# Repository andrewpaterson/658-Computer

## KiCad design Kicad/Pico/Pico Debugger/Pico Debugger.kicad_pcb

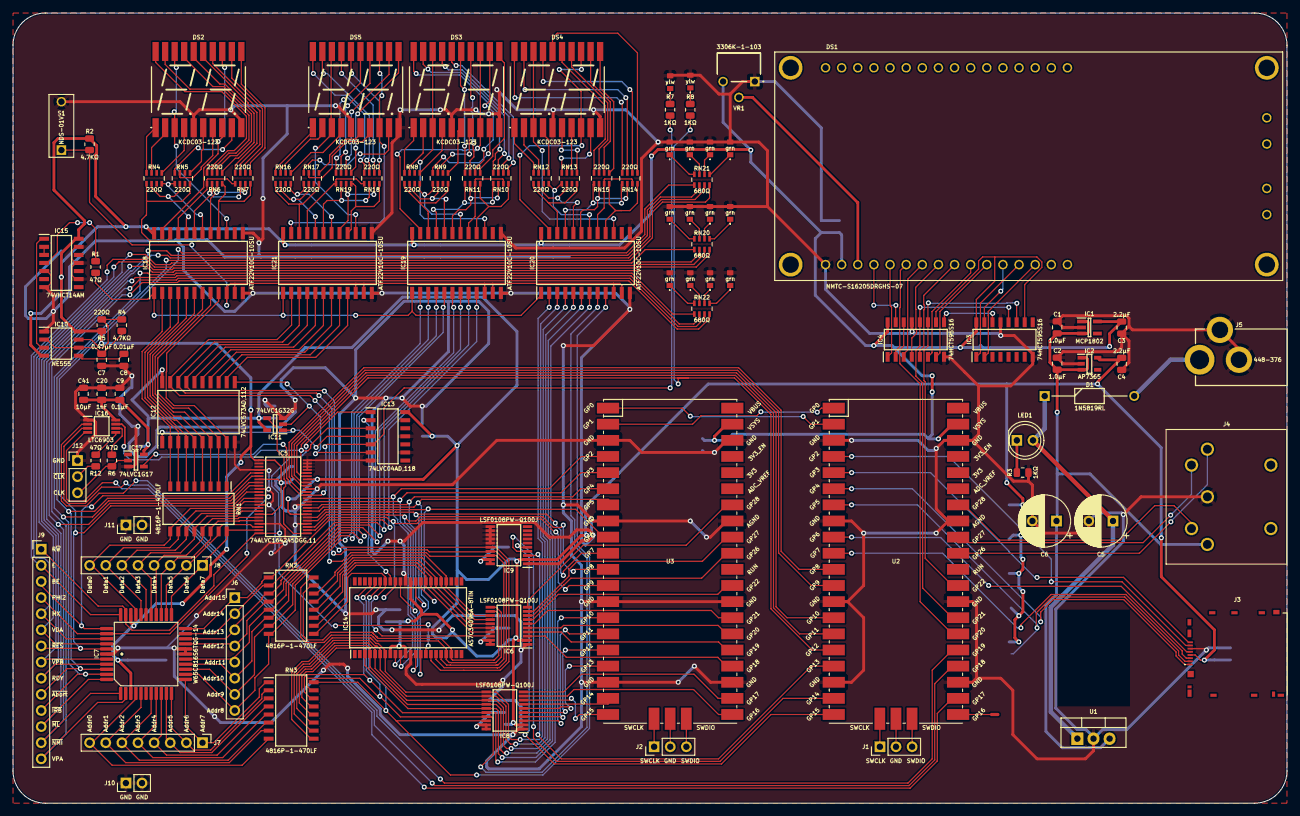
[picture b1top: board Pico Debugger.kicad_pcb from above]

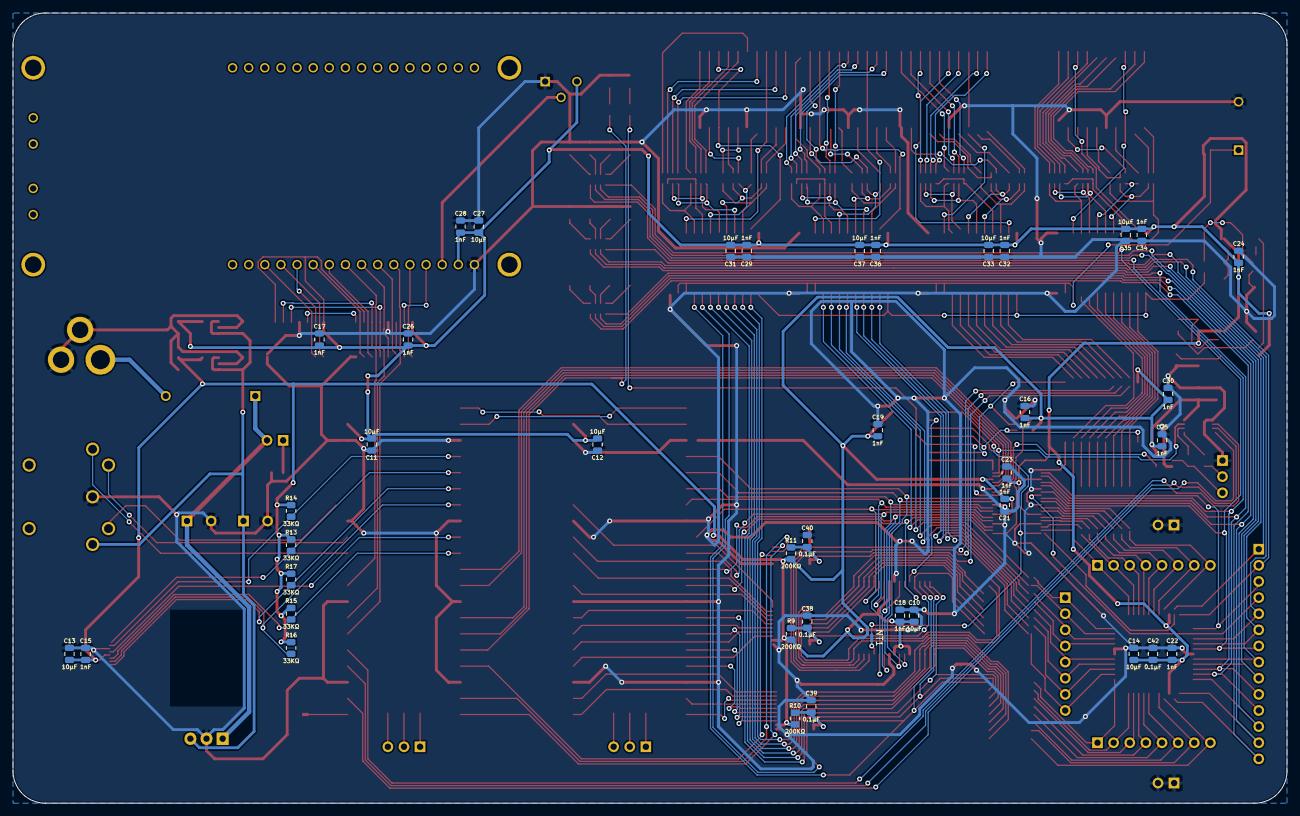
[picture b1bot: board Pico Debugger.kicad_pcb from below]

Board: 2 copper layers, 200.7 x 124.5 mm, 142 parts (40 on the bottom side), 273 nets.

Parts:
C1, C2, C3, C4, C7, C8, C9, C10, C11, C12, C13, C14, C15, C16, C17, C18, C19, C20, C21, C22, C23, C24, C25, C26, C27, C28, C29, C30, C31, C32, C33, C34, C35, C36, C37, C38, C39, C40, C41, C42: C_0805
C5, C6: C_Polarized; CP_Radial_D8.0mm_P3.80mm
D1: 1N5819RL; DIOAD1414W86L464D238
DS1: NMTC-S16205DRGHS-07; NMTCS16205DRGHS07_1
DS2, DS3, DS4, DS5: KCDC03-123; KCDC03123
IC1: MCP1802T-5002I_OT; SOT95P270X145-5N
IC2: AP7365-33WG-7; SOT95P285X130-5N
IC3, IC4: 74HCT595S16; SOIC127P600X175-16N
IC5: 74ALVC164245DGG,11; SOP50P810X120-48N
IC6, IC8, IC9: LSF0108PW-Q100J; SOP65P640X110-20N
IC7: W65C816S6TQG-14; W65C816 PLCC 0.8mm 44 Pin
IC10: NE555DRG4; SOIC127P600X175-8N
IC11: 74LVC1G32GV,125; SOT95P275X110-5N
IC12: 74LVC573AD,112; SOIC127P1032X265-20N
IC13: 74LVC04AD,118; SOIC127P600X175-14N
IC14: AS7C34096A-8TIN; SOP80P1176X120-44N
IC15: 74VHCT14AM; SOIC127P600X175-14N
IC16: LTC6903CMS8#PBF; SOP65P490X110-8N
IC17: 74LVC1G17GV,125; SOT95P275X110-5N
IC18, IC19, IC20, IC21: ATF22V10C-10SU; SOIC127P1032X265-24N
J1, J2, J12: Conn_01x03_Male; PinHeader_1x03_P2.54mm_Vertical
J3: SDHR-8BRS-K-363-A0-S-ETB(HF); SDHR8BRSK363A0SETBHF
J4: 491-087; 491087
J5: 448-376; 448376
J6, J7, J8: Conn_01x08_Male; PinHeader_1x08_P2.54mm_Vertical
J9: Conn_01x14_Male; PinHeader_1x14_P2.54mm_Vertical
J10, J11: Conn_01x02_Male; PinHeader_1x02_P2.54mm_Vertical
LED1: LED_Small_Filled; LED_D5.0mm
LED2, LED3: 150224YS73100A; 150224BS73100A
LED4, LED5, LED6, LED7, LED8, LED9, LED10, LED11, LED12, LED13, LED14, LED15: 150224VS73100A
NT1, NT2: NetTie; NetTie-2_SMD_Pad0.5mm
R1, R2, R3, R4, R5, R6, R7, R8, R9, R10, R11, R12, R13, R14, R15, R16, R17: R_0805
RN1, RN2, RN3: 4816P-1-470LF; SOIC127P762X240-16N
RN4, RN5, RN6, RN7, RN8, RN9, RN10, RN11, RN12, RN13, RN14, RN15, RN16, RN17, RN18, RN19: CAY16-221J4LF; CAY1647R0F4LF
RN20, RN21, RN22: CAY16-681J4LF; CAY16-J4
S1: NDS-01V; NDS01V
U1: L7805; TO-220-3_Vertical
U2, U3: Pico; RPi_Pico_SMD
VR1: 3306K-1-103; 3306K1103

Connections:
/3.3V: C4.1, C9.1, C10.1, C13.1, C15.1, C16.1, C18.1, C19.1, C20.1, C21.1, C25.1, C30.1, C41.1, IC2.5 (VOUT), IC5.31 (3V), IC5.42 (3V), IC6.2 (REFA), IC8.2 (REFA), IC9.2 (REFA), IC11.5 (3V), IC12.20 (3V), IC13.14 (3V), IC14.8 (~CE), IC14.11 (3V), IC14.33 (3V), IC16.8 (V+), IC17.5 (3V), J3.4 (VDD), R9.1, R10.1, R11.1, R13.2, R14.2, R15.2, R16.2, R17.2
/5V: C3.1, C11.1, C12.1, C14.1, C17.1, C22.1, C23.1, C24.1, C26.1, C27.1, C28.1, C29.1, C31.1, C32.1, C33.1, C34.1, C35.1, C36.1, C37.1, C42.1, DS1.2 (5V), IC1.5 (VOUT), IC3.10 (~MR), IC3.16 (VCC), IC4.10 (~MR), IC4.16 (VCC), IC5.1 (1DIR), IC5.7 (5V), IC5.18 (5V), IC7.9 (VCC), IC7.37 (VCC), IC10.4 (RESET), IC10.8 (VCC), IC15.14 (5V), IC18.24 (5V), IC19.24 (5V), IC20.24 (5V), IC21.24 (5V), R2.2, R5.2, U2.39 (VSYS), U3.39 (VSYS), VR1.3 (VIN)
/5V Forward: C5.1, D1.1, LED1.2 (A), U1.1 (IN)
/5V Source: C1.1, C2.1, C6.1, IC1.1 (VIN), IC1.3 (~SHDN), IC2.1 (VIN), IC2.3 (EN), J4.3, U1.3 (OUT)
/300Hz: IC18.1 (CLK/IN), IC19.1 (CLK/IN), IC20.1 (CLK/IN), IC21.1 (CLK/IN), R1.1
/Addr0: IC8.11 (B7), IC14.7 (A0), IC20.2 (IN0), RN3.9
/Addr0_{Pico}: IC8.10 (A7), U3.22 (GPIO17)
/Addr0_{W65}: IC7.10 (A0), J7.8, RN3.8
/Addr1: IC8.12 (B6), IC14.6 (A1), IC20.3 (IN1), RN3.10
/Addr1_{Pico}: IC8.9 (A6), U3.21 (GPIO16)
/Addr1_{W65}: IC7.11 (A1), J7.7, RN3.7
/Addr2: IC8.13 (B5), IC14.5 (A2), IC20.4 (IN2/PD), RN3.11
/Addr2_{Pico}: IC8.8 (A5), U3.20 (GPIO15)
/Addr2_{W65}: IC7.13 (A2), J7.6, RN3.6
/Addr3: IC8.14 (B4), IC14.4 (A3), IC20.5 (IN3), RN3.12
/Addr3_{Pico}: IC8.7 (A4), U3.19 (GPIO14)
/Addr3_{W65}: IC7.14 (A3), J7.5, RN3.5
/Addr4: IC8.15 (B3), IC14.3 (A4), IC20.6 (IN4), RN3.13
/Addr4_{Pico}: IC8.6 (A3), U3.17 (GPIO13)
/Addr4_{W65}: IC7.15 (A4), J7.4, RN3.4
/Addr5: IC8.16 (B2), IC14.41 (A5), IC20.7 (IN5), RN3.14
/Addr5_{Pico}: IC8.5 (A2), U3.16 (GPIO12)
/Addr5_{W65}: IC7.16 (A5), J7.3, RN3.3
/Addr6: IC8.17 (B1), IC14.40 (A6), IC20.8 (IN6), RN3.15
/Addr6_{Pico}: IC8.4 (A1), U3.15 (GPIO11)
/Addr6_{W65}: IC7.17 (A6), J7.2, RN3.2
/Addr7: IC8.18 (B0), IC14.39 (A7), IC20.9 (IN7), RN3.16
/Addr7_{Pico}: IC8.3 (A0), U3.14 (GPIO10)
/Addr7_{W65}: IC7.18 (A7), J7.1, RN3.1
/Addr8: IC6.18 (B0), IC14.38 (A8), RN2.9
/Addr8_{Pico}: IC6.3 (A0), U3.24 (GPIO18)
/Addr8_{W65}: IC7.19 (A8), IC19.2 (IN0), J6.8, RN2.8
/Addr9: IC6.17 (B1), IC14.30 (A9), RN2.10
/Addr9_{Pico}: IC6.4 (A1), U3.25 (GPIO19)
/Addr9_{W65}: IC7.20 (A9), IC19.3 (IN1), J6.7, RN2.7
/Addr10: IC6.16 (B2), IC14.29 (A10), RN2.11
/Addr10_{Pico}: IC6.5 (A2), U3.26 (GPIO20)
/Addr10_{W65}: IC7.21 (A10), IC19.4 (IN2/PD), J6.6, RN2.6
/Addr11: IC6.15 (B3), IC14.28 (A11), RN2.12
/Addr11_{Pico}: IC6.6 (A3), U3.27 (GPIO21)
/Addr11_{W65}: IC7.22 (A11), IC19.5 (IN3), J6.5, RN2.5
/Addr12: IC6.14 (B4), IC14.27 (A12), RN2.13
/Addr12_{Pico}: IC6.7 (A4), U3.29 (GPIO22)
/Addr12_{W65}: IC7.25 (A12), IC19.6 (IN4), J6.4, RN2.4
/Addr13: IC6.13 (B5), IC14.26 (A13), RN2.14
/Addr13_{Pico}: IC6.8 (A5), U3.31 (GPIO26_ADC0)
/Addr13_{W65}: IC7.26 (A13), IC19.7 (IN5), J6.3, RN2.3
/Addr14: IC6.12 (B6), IC14.20 (A14), RN2.15
/Addr14_{Pico}: IC6.9 (A6), U3.32 (GPIO27_ADC1)
/Addr14_{W65}: IC7.27 (A14), IC19.8 (IN6), J6.2, RN2.2
/Addr15: IC6.11 (B7), IC14.19 (A15), RN2.16
/Addr15_{Pico}: IC6.10 (A7), U3.34 (GPIO28_ADC2)
/Addr15_{W65}: IC7.28 (A15), IC19.9 (IN7), J6.1, RN2.1
/Addr16: IC9.18 (B0), IC12.19 (Q0), IC14.18 (A16), IC21.2 (IN0)
/Addr16_{Pico}: IC9.3 (A0), U2.17 (GPIO13)
/Addr17: IC9.17 (B1), IC12.18 (Q1), IC14.17 (A17), IC21.3 (IN1)
/Addr17_{Pico}: IC9.4 (A1), U2.19 (GPIO14)
/Addr18: IC9.16 (B2), IC12.17 (Q2), IC14.16 (A18), IC21.4 (IN2/PD)
/Addr18_{Pico}: IC9.5 (A2), U2.20 (GPIO15)
/Addr19: IC12.16 (Q3), IC21.5 (IN3)
/Addr20: IC12.15 (Q4), IC21.6 (IN4)
/Addr21: IC12.14 (Q5), IC21.7 (IN5)
/Addr22: IC12.13 (Q6), IC21.8 (IN6)
/Addr23: IC12.12 (Q7), IC21.9 (IN7)
/BE: IC5.44 (1A2), IC13.3 (2A), IC16.7 (OE), R8.1, U2.16 (GPIO12)
/BE_{W65}: IC5.5 (1B2), IC7.40 (BE), J9.3
/Bank Address Display/Digit 0 A Seg: IC21.17 (I/O3), RN18.7 (R2), RN19.7 (R2)
/Bank Address Display/Digit 0 B Seg: IC21.16 (I/O2), RN18.8 (R1), RN19.8 (R1)
/Bank Address Display/Digit 0 C Seg: IC21.18 (I/O4), RN16.4 (R4), RN17.1 (R1)
/Bank Address Display/Digit 0 D Seg: IC21.20 (I/O6), RN16.2 (R2), RN17.2 (R2)
/Bank Address Display/Digit 0 E Seg: IC21.22 (I/O8), RN16.1 (R1), RN17.4 (R4)
/Bank Address Display/Digit 0 F Seg: IC21.19 (I/O5), RN18.6 (R3), RN19.6 (R3)
/Bank Address Display/Digit 0 G Seg: IC21.21 (I/O7), RN18.5 (R4), RN19.5 (R4)
/Bank Address Display/Digit L0 Cathode: DS5.3 (Cathode_{(Left)}), DS5.18 (Cathode_{(Left)}), IC21.15 (I/O1)
/Bank Address Display/Digit R0 Cathode: DS5.8 (Cathode_{(Right)}), DS5.13 (Cathode_{(Right)}), IC21.23 (I/O9)
/Clk: IC16.6 (CLK), R6.1
/Data0: IC5.36 (2A0), IC14.9 (DQ0), U3.4 (GPIO2)
/Data0_{W65}: IC5.13 (2B0), IC7.36 (D0), J8.8, RN1.9
/Data1: IC5.35 (2A1), IC14.10 (DQ1), U3.5 (GPIO3)
/Data1_{W65}: IC5.14 (2B1), IC7.35 (D1), J8.7, RN1.10
/Data2: IC5.33 (2A2), IC14.13 (DQ2), U3.6 (GPIO4)
/Data2_{W65}: IC5.16 (2B2), IC7.34 (D2), J8.6, RN1.11
/Data3: IC5.32 (2A3), IC14.14 (DQ3), U3.7 (GPIO5)
/Data3_{W65}: IC5.17 (2B3), IC7.33 (D3), J8.5, RN1.12
/Data4: IC5.30 (2A4), IC14.31 (DQ4), U3.9 (GPIO6)
/Data4_{W65}: IC5.19 (2B4), IC7.32 (D4), J8.4, RN1.13
/Data5: IC5.29 (2A5), IC14.32 (DQ5), U3.10 (GPIO7)
/Data5_{W65}: IC5.20 (2B5), IC7.31 (D5), J8.3, RN1.14
/Data6: IC5.27 (2A6), IC14.35 (DQ6), U3.11 (GPIO8)
/Data6_{W65}: IC5.22 (2B6), IC7.30 (D6), J8.2, RN1.15
/Data7: IC5.26 (2A7), IC14.36 (DQ7), U3.12 (GPIO9)
/Data7_{W65}: IC5.23 (2B7), IC7.29 (D7), J8.1, RN1.16
/Data Display/Digit 0 A Seg: IC18.17 (I/O3), RN6.7 (R2), RN7.7 (R2)
/Data Display/Digit 0 B Seg: IC18.16 (I/O2), RN6.8 (R1), RN7.8 (R1)
/Data Display/Digit 0 C Seg: IC18.18 (I/O4), RN4.4 (R4), RN5.1 (R1)
/Data Display/Digit 0 D Seg: IC18.20 (I/O6), RN4.2 (R2), RN5.2 (R2)
/Data Display/Digit 0 E Seg: IC18.22 (I/O8), RN4.1 (R1), RN5.4 (R4)
/Data Display/Digit 0 F Seg: IC18.19 (I/O5), RN6.6 (R3), RN7.6 (R3)
/Data Display/Digit 0 G Seg: IC18.21 (I/O7), RN6.5 (R4), RN7.5 (R4)
/Data Display/Digit L0 Cathode: DS2.3 (Cathode_{(Left)}), DS2.18 (Cathode_{(Left)}), IC18.15 (I/O1)
/Data Display/Digit R0 Cathode: DS2.8 (Cathode_{(Right)}), DS2.13 (Cathode_{(Right)}), IC18.23 (I/O9)
/E: IC7.39 (E), J9.2, RN20.2 (R2)
/GND: C1.2, C2.2, C3.2, C4.2, C5.2, C6.2, C7.2, C8.2, C9.2, C10.2, C11.2, C12.2, C13.2, C14.2, C15.2, C16.2, C17.2, C18.2, C19.2, C20.2, C21.2, C22.2, C23.2, C24.2, C25.2, C26.2, C27.2, C28.2, C29.2, C30.2, C31.2, C32.2, C33.2, C34.2, C35.2, C36.2, C37.2, C38.2, C39.2, C40.2, C41.2, C42.2, DS1.1 (GND), DS2.5 (Dot_{(Left)}), DS2.10 (Dot_{(Right)}), DS3.5 (Dot_{(Left)}), DS3.10 (Dot_{(Right)}), DS4.5 (Dot_{(Left)}), DS4.10 (Dot_{(Right)}), DS5.5 (Dot_{(Left)}), DS5.10 (Dot_{(Right)}), IC1.2 (VSS), IC2.2 (GND), IC3.8 (GND), IC3.13 (~OE), IC4.8 (GND), IC4.13 (~OE), IC5.4 (GND), IC5.10 (GND), IC5.15 (GND), IC5.21 (GND), IC5.28 (GND), IC5.34 (GND), IC5.39 (GND), IC5.45 (GND), IC5.46 (1A1), IC5.47 (1A0), IC5.48 (1~OE), IC6.1 (GND), IC7.1 (GND), IC7.23 (GND), IC7.24 (GND), IC8.1 (GND), IC9.1 (GND), IC9.11 (B7), IC9.12 (B6), IC9.13 (B5), IC9.14 (B4), IC9.15 (B3), IC10.1 (GND), IC11.3 (GND), IC12.10 (GND), IC13.7 (GND), IC13.9 (4A), IC13.11 (5A), IC13.13 (6A), IC14.12 (GND), IC14.34 (GND), IC15.5 (3A), IC15.7 (GND), IC15.9 (4A), IC15.11 (5A), IC15.13 (6A), IC16.1 (GND), IC17.3 (GND), IC18.12 (GND), IC18.13 (IN10), IC19.12 (GND), IC19.13 (IN10), IC20.12 (GND), IC20.13 (IN10), IC21.12 (GND), IC21.13 (IN10), J3.6 (VSS), J4.2, J5.B1 (GND), J5.C1 (GND), J10.1, J10.2, J11.1, J11.2, J12.1, LED2.2, LED3.2, LED4.2, LED5.2, LED6.2, LED7.2, LED8.2, LED9.2, LED10.2, LED11.2, LED12.2, LED13.2, LED14.2, LED15.2, R3.1, S1.2 (NO), U1.2 (GND), U2.3 (GND), U2.8 (GND), U2.13 (GND), U2.18 (GND), U2.23 (GND), U2.28 (GND), U2.33 (AGND), U2.38 (GND), U3.3 (GND), U3.8 (GND), U3.13 (GND), U3.18 (GND), U3.23 (GND), U3.28 (GND), U3.33 (AGND), U3.38 (GND), VR1.1 (GND)
/High Address Display/Digit 0 A Seg: IC19.17 (I/O3), RN10.7 (R2), RN11.7 (R2)
/High Address Display/Digit 0 B Seg: IC19.16 (I/O2), RN10.8 (R1), RN11.8 (R1)
/High Address Display/Digit 0 C Seg: IC19.18 (I/O4), RN8.4 (R4), RN9.1 (R1)
/High Address Display/Digit 0 D Seg: IC19.20 (I/O6), RN8.2 (R2), RN9.2 (R2)
/High Address Display/Digit 0 E Seg: IC19.22 (I/O8), RN8.1 (R1), RN9.4 (R4)
/High Address Display/Digit 0 F Seg: IC19.19 (I/O5), RN10.6 (R3), RN11.6 (R3)
/High Address Display/Digit 0 G Seg: IC19.21 (I/O7), RN10.5 (R4), RN11.5 (R4)
/High Address Display/Digit L0 Cathode: DS3.3 (Cathode_{(Left)}), DS3.18 (Cathode_{(Left)}), IC19.15 (I/O1)
/High Address Display/Digit R0 Cathode: DS3.8 (Cathode_{(Right)}), DS3.13 (Cathode_{(Right)}), IC19.23 (I/O9)
/Keypad CP: J4.4, U2.32 (GPIO27_ADC1)
/Keypad PL: J4.1, U2.31 (GPIO26_ADC0)
/Keypad Q_{IN}: J4.5, U2.34 (GPIO28_ADC2)
/LCD Bit Out: IC4.14 (DS), U2.26 (GPIO20)
/LCD DB0: DS1.7 (DB0), IC4.3 (Q3)
/LCD DB1: DS1.8 (DB1), IC4.4 (Q4)
/LCD DB2: DS1.9 (DB2), IC4.5 (Q5)
/LCD DB3: DS1.10 (DB3), IC4.6 (Q6)
/LCD DB4: DS1.11 (DB4), IC4.7 (Q7)
/LCD DB5: DS1.12 (DB5), IC3.15 (Q0)
/LCD DB6: DS1.13 (DB6), IC3.1 (Q1)
/LCD DB7: DS1.14 (DB7), IC3.2 (Q2)
/LCD E: DS1.6 (E), IC4.2 (Q2)
/LCD RS: DS1.4 (RS), IC4.15 (Q0)
/LCD R~W: DS1.5 (R/~W), IC4.1 (Q1)
/LCD Shift Clock: IC3.11 (SHCP), IC4.11 (SHCP), U2.29 (GPIO22)
/LCD Store Clock: IC3.12 (STCP), IC4.12 (STCP), U2.27 (GPIO21)
/Low Address Display/Digit 0 A Seg: IC20.17 (I/O3), RN14.7 (R2), RN15.7 (R2)
/Low Address Display/Digit 0 B Seg: IC20.16 (I/O2), RN14.8 (R1), RN15.8 (R1)
/Low Address Display/Digit 0 C Seg: IC20.18 (I/O4), RN12.4 (R4), RN13.1 (R1)
/Low Address Display/Digit 0 D Seg: IC20.20 (I/O6), RN12.2 (R2), RN13.2 (R2)
/Low Address Display/Digit 0 E Seg: IC20.22 (I/O8), RN12.1 (R1), RN13.4 (R4)
/Low Address Display/Digit 0 F Seg: IC20.19 (I/O5), RN14.6 (R3), RN15.6 (R3)
/Low Address Display/Digit 0 G Seg: IC20.21 (I/O7), RN14.5 (R4), RN15.5 (R4)
/Low Address Display/Digit L0 Cathode: DS4.3 (Cathode_{(Left)}), DS4.18 (Cathode_{(Left)}), IC20.15 (I/O1)
/Low Address Display/Digit R0 Cathode: DS4.8 (Cathode_{(Right)}), DS4.13 (Cathode_{(Right)}), IC20.23 (I/O9)
/MX: IC7.42 (MX), J9.5, RN20.3 (R3)
/PHI2: IC5.37 (1A7), IC13.5 (3A), IC17.4 (Y), R7.1
/PHI2_{W65}: IC5.12 (1B7), IC7.41 (PHI2), J9.4
/Q7S: IC3.14 (DS), IC4.9 (Q7S)
/RDY: IC7.3 (RDY), J9.9, RN21.3 (R3)
/R~W: IC5.24 (2DIR), IC7.38 (R~W), IC13.1 (1A), J9.1, NT1.1, RN20.1 (R1)
/SD Clk: J3.5 (CLK), U2.9 (GPIO6)
/SD Cmd: J3.3 (CMD), R15.1, U2.10 (GPIO7)
/SD Dat0: J3.7 (DAT0), R14.1, U2.4 (GPIO2)
/SD Dat1: J3.8 (DAT1), R13.1, U2.5 (GPIO3)
/SD Dat2: J3.1 (DAT2), R17.1, U2.6 (GPIO4)
/SD Dat3: J3.2 (CD/DAT3), R16.1, U2.7 (GPIO5)
/SPI_{0} CS: IC16.4 (~SEN), U2.22 (GPIO17)
/SPI_{0} RX: NT2.1, U2.21 (GPIO16)
/SPI_{0} SCK: IC16.3 (SCK), U2.24 (GPIO18)
/SPI_{0} TX: IC16.2 (SDI), U2.25 (GPIO19)
/Tame Clk: IC17.2 (A), J12.3, R6.2
/Tame Data0: IC12.2 (D0), IC18.2 (IN0), RN1.8
/Tame Data1: IC12.3 (D1), IC18.3 (IN1), RN1.7
/Tame Data2: IC12.4 (D2), IC18.4 (IN2/PD), RN1.6
/Tame Data3: IC12.5 (D3), IC18.5 (IN3), RN1.5
/Tame Data4: IC12.6 (D4), IC18.6 (IN4), RN1.4
/Tame Data5: IC12.7 (D5), IC18.7 (IN5), RN1.3
/Tame Data6: IC12.8 (D6), IC18.8 (IN6), RN1.2
/Tame Data7: IC12.9 (D7), IC18.9 (IN7), RN1.1
/UART 1: U2.1 (GPIO0), U3.2 (GPIO1)
/UART 2: U2.2 (GPIO1), U3.1 (GPIO0)
/VDA: IC7.43 (VDA), J9.6, RN20.4 (R4)
/VPA: IC7.8 (VPA), J9.14, RN22.4 (R4)
/V_{0}: DS1.3 (V_{O}), VR1.2 (VOUT)
/~ABORT: IC5.43 (1A3), U2.15 (GPIO11)
/~ABORT_{W65}: IC5.6 (1B3), IC7.4 (~ABORT), J9.10, RN21.4 (R4)
/~BE: IC11.1 (B), IC12.1 (~OE), IC13.4 (2Y)
/~BE+~PHI2: IC5.25 (2~OE), IC11.4 (Y)
/~IRQ: IC5.41 (1A4), U2.14 (GPIO10)
/~IRQ_{W65}: IC5.8 (1B4), IC7.5 (~IRQ), J9.11, RN22.1 (R1)
/~LED Enable: IC18.10 (IN8), IC18.11 (IN9), IC19.10 (IN8), IC19.11 (IN9), IC20.10 (IN8), IC20.11 (IN9), IC21.10 (IN8), IC21.11 (IN9), R2.1, S1.1 (COM)
/~ML: IC7.6 (~ML), J9.12, RN22.2 (R2)
/~NMI: IC5.40 (1A5), U2.12 (GPIO9)
/~NMI_{W65}: IC5.9 (1B5), IC7.7 (~NMI), J9.13, RN22.3 (R3)
/~OE: IC13.2 (1Y), IC14.37 (~OE)
/~PHI2: IC11.2 (A), IC12.11 (LE), IC13.6 (3Y)
/~RES: IC5.38 (1A6), U2.11 (GPIO8)
/~RES_{W65}: IC5.11 (1B6), IC7.44 (~RES), J9.7, RN21.1 (R1)
/~VP: IC7.2 (~VP), J9.8, RN21.2 (R2)
/~WE: IC14.15 (~WE), NT1.2
unnamed: C7.1, IC10.2 (TRIG), IC10.6 (THRES), R4.1
unnamed: C8.1, IC10.5 (CONT)
unnamed: C38.1, IC6.19 (REFB), IC6.20 (EN), R9.2
unnamed: C39.1, IC8.19 (REFB), IC8.20 (EN), R10.2
unnamed: C40.1, IC9.19 (REFB), IC9.20 (EN), R11.2
unnamed: D1.2, J5.A1 (VCC)
unnamed: DS2.1 (E-Seg_{(Left)}), RN4.8 (R1)
unnamed: DS2.2 (D-Seg_{(Left)}), RN4.7 (R2)
unnamed: DS2.4 (C-Seg_{(Left)}), RN4.5 (R4)
unnamed: DS2.6 (E-Seg_{(Right)}), RN5.5 (R4)
unnamed: DS2.7 (D-Seg_{(Right)}), RN5.7 (R2)
unnamed: DS2.9 (C-Seg_{(Right)}), RN5.8 (R1)
unnamed: DS2.11 (B-Seg_{(Right)}), RN7.1 (R1)
unnamed: DS2.12 (A-Seg_{(Right)}), RN7.2 (R2)
unnamed: DS2.14 (F-Seg_{(Right)}), RN7.3 (R3)
unnamed: DS2.15 (G-Seg_{(Right)}), RN7.4 (R4)
unnamed: DS2.16 (B-Seg_{(Left)}), RN6.1 (R1)
unnamed: DS2.17 (A-Seg_{(Left)}), RN6.2 (R2)
unnamed: DS2.19 (F-Seg_{(Left)}), RN6.3 (R3)
unnamed: DS2.20 (G-Seg_{(Left)}), RN6.4 (R4)
unnamed: DS3.1 (E-Seg_{(Left)}), RN8.8 (R1)
unnamed: DS3.2 (D-Seg_{(Left)}), RN8.7 (R2)
unnamed: DS3.4 (C-Seg_{(Left)}), RN8.5 (R4)
unnamed: DS3.6 (E-Seg_{(Right)}), RN9.5 (R4)
unnamed: DS3.7 (D-Seg_{(Right)}), RN9.7 (R2)
unnamed: DS3.9 (C-Seg_{(Right)}), RN9.8 (R1)
unnamed: DS3.11 (B-Seg_{(Right)}), RN11.1 (R1)
unnamed: DS3.12 (A-Seg_{(Right)}), RN11.2 (R2)
unnamed: DS3.14 (F-Seg_{(Right)}), RN11.3 (R3)
unnamed: DS3.15 (G-Seg_{(Right)}), RN11.4 (R4)
unnamed: DS3.16 (B-Seg_{(Left)}), RN10.1 (R1)
unnamed: DS3.17 (A-Seg_{(Left)}), RN10.2 (R2)
unnamed: DS3.19 (F-Seg_{(Left)}), RN10.3 (R3)
unnamed: DS3.20 (G-Seg_{(Left)}), RN10.4 (R4)
unnamed: DS4.1 (E-Seg_{(Left)}), RN12.8 (R1)
unnamed: DS4.2 (D-Seg_{(Left)}), RN12.7 (R2)
unnamed: DS4.4 (C-Seg_{(Left)}), RN12.5 (R4)
unnamed: DS4.6 (E-Seg_{(Right)}), RN13.5 (R4)
unnamed: DS4.7 (D-Seg_{(Right)}), RN13.7 (R2)
unnamed: DS4.9 (C-Seg_{(Right)}), RN13.8 (R1)
unnamed: DS4.11 (B-Seg_{(Right)}), RN15.1 (R1)
unnamed: DS4.12 (A-Seg_{(Right)}), RN15.2 (R2)
unnamed: DS4.14 (F-Seg_{(Right)}), RN15.3 (R3)
unnamed: DS4.15 (G-Seg_{(Right)}), RN15.4 (R4)
unnamed: DS4.16 (B-Seg_{(Left)}), RN14.1 (R1)
unnamed: DS4.17 (A-Seg_{(Left)}), RN14.2 (R2)
unnamed: DS4.19 (F-Seg_{(Left)}), RN14.3 (R3)
unnamed: DS4.20 (G-Seg_{(Left)}), RN14.4 (R4)
unnamed: DS5.1 (E-Seg_{(Left)}), RN16.8 (R1)
unnamed: DS5.2 (D-Seg_{(Left)}), RN16.7 (R2)
unnamed: DS5.4 (C-Seg_{(Left)}), RN16.5 (R4)
unnamed: DS5.6 (E-Seg_{(Right)}), RN17.5 (R4)
unnamed: DS5.7 (D-Seg_{(Right)}), RN17.7 (R2)
unnamed: DS5.9 (C-Seg_{(Right)}), RN17.8 (R1)
unnamed: DS5.11 (B-Seg_{(Right)}), RN19.1 (R1)
unnamed: DS5.12 (A-Seg_{(Right)}), RN19.2 (R2)
unnamed: DS5.14 (F-Seg_{(Right)}), RN19.3 (R3)
unnamed: DS5.15 (G-Seg_{(Right)}), RN19.4 (R4)
unnamed: DS5.16 (B-Seg_{(Left)}), RN18.1 (R1)
unnamed: DS5.17 (A-Seg_{(Left)}), RN18.2 (R2)
unnamed: DS5.19 (F-Seg_{(Left)}), RN18.3 (R3)
unnamed: DS5.20 (G-Seg_{(Left)}), RN18.4 (R4)
unnamed: IC10.3 (OUT), IC15.1 (1A)
unnamed: IC10.7 (DISCH), R4.2, R5.1
unnamed: IC15.2 (1Y), IC15.3 (2A)
unnamed: IC15.4 (2Y), R1.2
unnamed: IC16.5 (~CLK), R12.1
unnamed: J1.1, U2.41 (SWCLK)
unnamed: J1.2, U2.42 (GND)
unnamed: J1.3, U2.43 (SWDIO)
unnamed: J2.1, U3.41 (SWCLK)
unnamed: J2.2, U3.42 (GND)
unnamed: J2.3, U3.43 (SWDIO)
unnamed: J12.2, R12.2
unnamed: LED1.1 (K), R3.2
unnamed: LED2.1, R7.2
unnamed: LED3.1, R8.2
unnamed: LED4.1, RN20.8 (R1)
unnamed: LED5.1, RN20.7 (R2)
unnamed: LED6.1, RN20.6 (R3)
unnamed: LED7.1, RN20.5 (R4)
unnamed: LED8.1, RN21.8 (R1)
unnamed: LED9.1, RN21.7 (R2)
unnamed: LED10.1, RN21.6 (R3)
unnamed: LED11.1, RN21.5 (R4)
unnamed: LED12.1, RN22.8 (R1)
unnamed: LED13.1, RN22.7 (R2)
unnamed: LED14.1, RN22.6 (R3)
unnamed: LED15.1, RN22.5 (R4)

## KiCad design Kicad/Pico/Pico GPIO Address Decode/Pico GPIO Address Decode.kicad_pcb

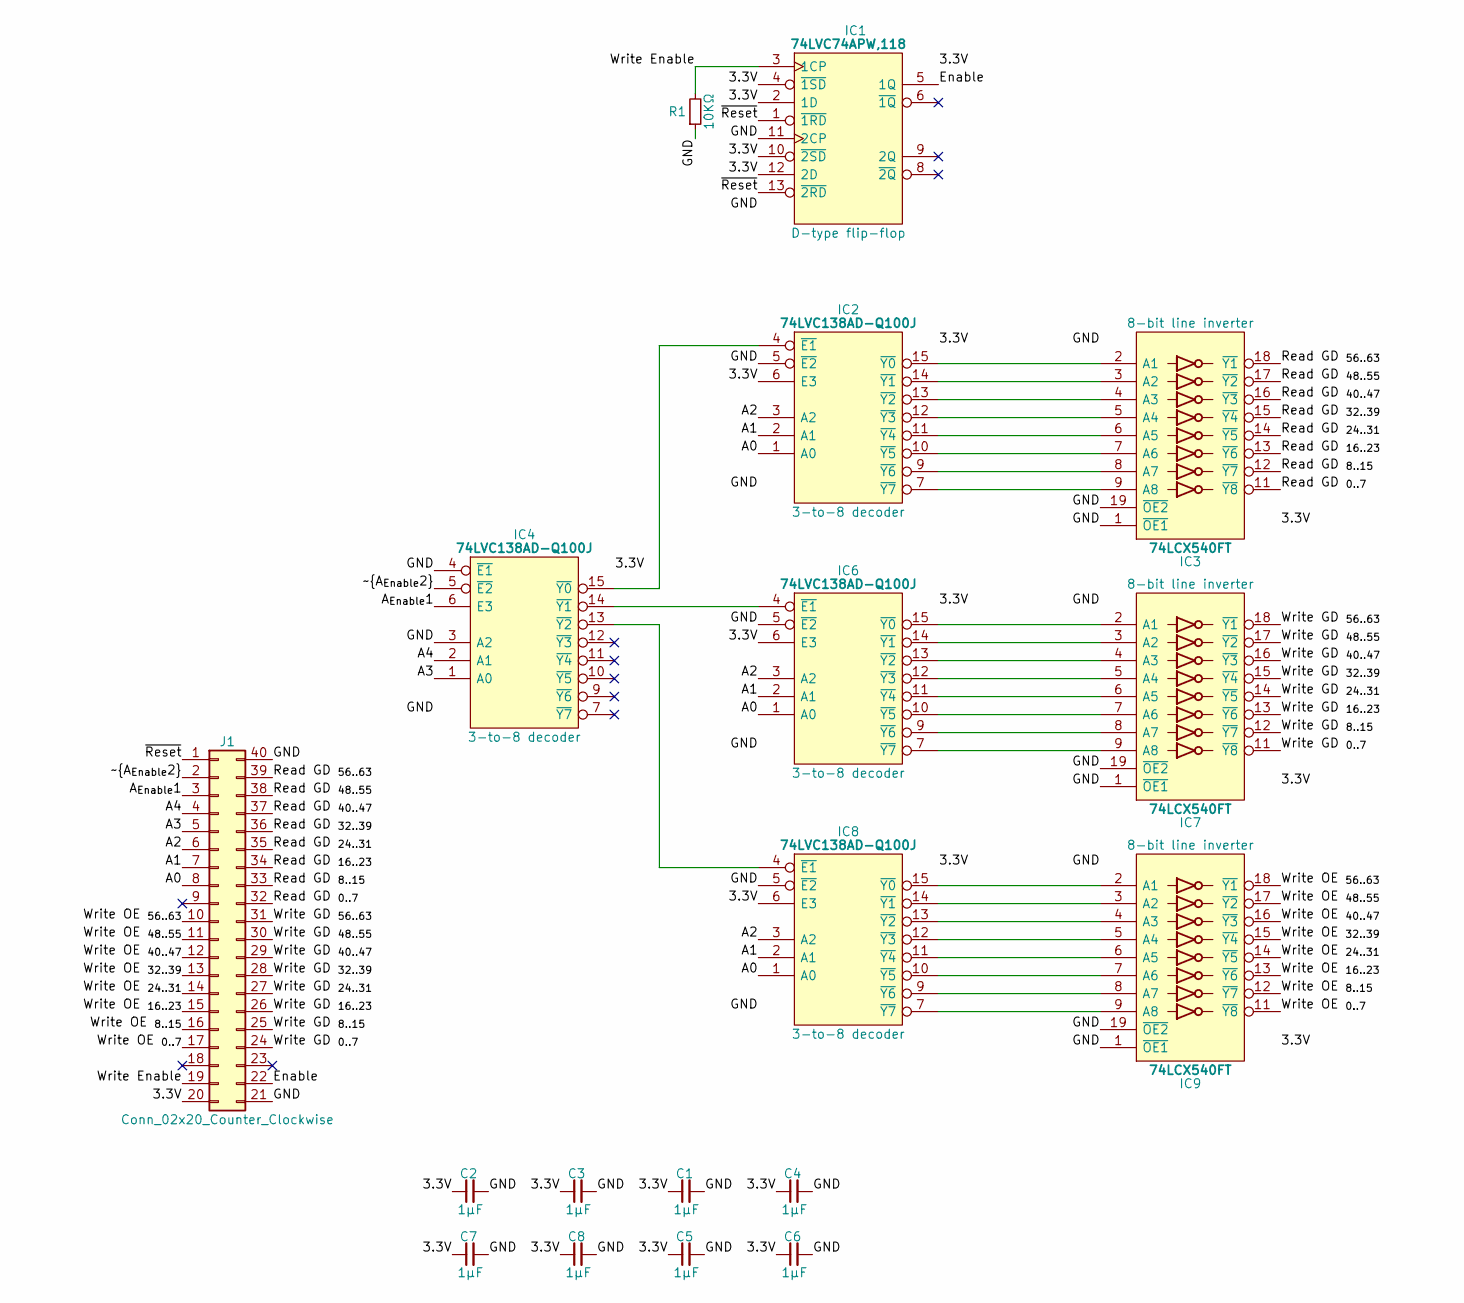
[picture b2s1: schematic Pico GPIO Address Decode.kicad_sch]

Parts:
C1, C2, C3, C4, C5, C6, C7, C8: 1μF; C_0805
IC1: 74LVC74APW,118; SOP65P640X110-14N; Mouser Part Number 771-74LVC74APW-T
IC2, IC4, IC6, IC8: 74LVC138AD-Q100J; SOIC127P600X175-16N; Mouser Part Number 771-74LVC138ADQ100J
IC3, IC7, IC9: 74LCX540FT; SOP65P640X120-20N; Manufacturer_Part_Number 74LCX540FT; Mouser Part Number 757-74LCX540FT
J1: Conn_02x20_Counter_Clockwise; DIP-40_Board_W22.86mm
R1: 10KΩ; R_0805

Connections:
/3.3V: C1.1, C2.1, C3.1, C4.1, C5.1, C6.1, C7.1, C8.1, IC1.2 (1D), IC1.4 (~1SD), IC1.10 (~2SD), IC1.12 (2D), IC1.14 (3V), IC2.6 (E3), IC2.16 (3V), IC3.20 (3V), IC4.16 (3V), IC6.6 (E3), IC6.16 (3V), IC7.20 (3V), IC8.6 (E3), IC8.16 (3V), IC9.20 (3V), J1.20
/A0: IC2.1 (A0), IC6.1 (A0), IC8.1 (A0), J1.8
/A1: IC2.2 (A1), IC6.2 (A1), IC8.2 (A1), J1.7
/A2: IC2.3 (A2), IC6.3 (A2), IC8.3 (A2), J1.6
/A3: IC4.1 (A0), J1.5
/A4: IC4.2 (A1), J1.4
/A_{Enable}1: IC4.6 (E3), J1.3
/Enable: IC1.5 (1Q), J1.22
/GND: C1.2, C2.2, C3.2, C4.2, C5.2, C6.2, C7.2, C8.2, IC1.7 (GND), IC1.11 (2CP), IC2.5 (~E2), IC2.8 (GND), IC3.1 (~OE1), IC3.10 (GND), IC3.19 (~OE2), IC4.3 (A2), IC4.4 (~E1), IC4.8 (GND), IC6.5 (~E2), IC6.8 (GND), IC7.1 (~OE1), IC7.10 (GND), IC7.19 (~OE2), IC8.5 (~E2), IC8.8 (GND), IC9.1 (~OE1), IC9.10 (GND), IC9.19 (~OE2), J1.21, J1.40, R1.1
/Read GD _{0..7}: IC3.11 (~Y8), J1.32
/Read GD _{8..15}: IC3.12 (~Y7), J1.33
/Read GD _{16..23}: IC3.13 (~Y6), J1.34
/Read GD _{24..31}: IC3.14 (~Y5), J1.35
/Read GD _{32..39}: IC3.15 (~Y4), J1.36
/Read GD _{40..47}: IC3.16 (~Y3), J1.37
/Read GD _{48..55}: IC3.17 (~Y2), J1.38
/Read GD _{56..63}: IC3.18 (~Y1), J1.39
/Write Enable: IC1.3 (1CP), J1.19, R1.2
/Write GD _{0..7}: IC7.11 (~Y8), J1.24
/Write GD _{8..15}: IC7.12 (~Y7), J1.25
/Write GD _{16..23}: IC7.13 (~Y6), J1.26
/Write GD _{24..31}: IC7.14 (~Y5), J1.27
/Write GD _{32..39}: IC7.15 (~Y4), J1.28
/Write GD _{40..47}: IC7.16 (~Y3), J1.29
/Write GD _{48..55}: IC7.17 (~Y2), J1.30
/Write GD _{56..63}: IC7.18 (~Y1), J1.31
/Write OE _{0..7}: IC9.11 (~Y8), J1.17
/Write OE _{8..15}: IC9.12 (~Y7), J1.16
/Write OE _{16..23}: IC9.13 (~Y6), J1.15
/Write OE _{24..31}: IC9.14 (~Y5), J1.14
/Write OE _{32..39}: IC9.15 (~Y4), J1.13
/Write OE _{40..47}: IC9.16 (~Y3), J1.12
/Write OE _{48..55}: IC9.17 (~Y2), J1.11
/Write OE _{56..63}: IC9.18 (~Y1), J1.10
/~A_{Enable2}: IC4.5 (~E2), J1.2
/~Reset: IC1.1 (~1RD), IC1.13 (~2RD), J1.1
unnamed: IC2.4 (~E1), IC4.15 (~Y0)
unnamed: IC2.15 (~Y0), IC3.2 (A1)
unnamed: IC2.14 (~Y1), IC3.3 (A2)
unnamed: IC2.13 (~Y2), IC3.4 (A3)
unnamed: IC2.12 (~Y3), IC3.5 (A4)
unnamed: IC2.11 (~Y4), IC3.6 (A5)
unnamed: IC2.10 (~Y5), IC3.7 (A6)
unnamed: IC2.9 (~Y6), IC3.8 (A7)
unnamed: IC2.7 (~Y7), IC3.9 (A8)
unnamed: IC4.14 (~Y1), IC6.4 (~E1)
unnamed: IC4.13 (~Y2), IC8.4 (~E1)
unnamed: IC6.15 (~Y0), IC7.2 (A1)
unnamed: IC6.14 (~Y1), IC7.3 (A2)
unnamed: IC6.13 (~Y2), IC7.4 (A3)
unnamed: IC6.12 (~Y3), IC7.5 (A4)
unnamed: IC6.11 (~Y4), IC7.6 (A5)
unnamed: IC6.10 (~Y5), IC7.7 (A6)
unnamed: IC6.9 (~Y6), IC7.8 (A7)
unnamed: IC6.7 (~Y7), IC7.9 (A8)
unnamed: IC8.15 (~Y0), IC9.2 (A1)
unnamed: IC8.14 (~Y1), IC9.3 (A2)
unnamed: IC8.13 (~Y2), IC9.4 (A3)
unnamed: IC8.12 (~Y3), IC9.5 (A4)
unnamed: IC8.11 (~Y4), IC9.6 (A5)
unnamed: IC8.10 (~Y5), IC9.7 (A6)
unnamed: IC8.9 (~Y6), IC9.8 (A7)
unnamed: IC8.7 (~Y7), IC9.9 (A8)

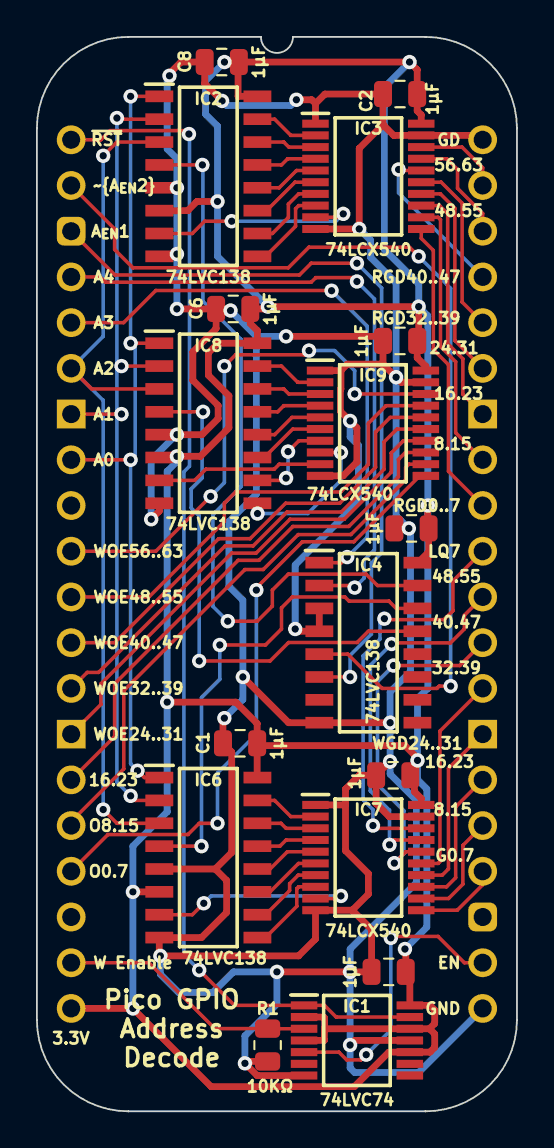
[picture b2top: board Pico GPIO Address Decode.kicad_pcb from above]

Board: 2 copper layers, 26.7 x 59.7 mm, 18 parts (0 on the bottom side), 63 nets.
